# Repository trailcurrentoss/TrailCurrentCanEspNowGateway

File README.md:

# TrailCurrent CAN to ESP-NOW Gateway

A wireless relay gateway that bridges CAN bus messages to ESP-NOW protocol for remote vehicle monitoring in tow vehicles. Part of the [TrailCurrent](https://trailcurrent.com) open-source vehicle platform.

## Overview

This project enables wireless relaying of CAN bus messages using the ESP-NOW protocol. The gateway hardware and firmware allow real-time data from a trailer's CAN bus to be transmitted reliably to remote displays and monitoring devices in a vehicle.

**Use Case:** Display trailer sensor data (battery voltage, temperature, weight sensors, etc.) on an in-vehicle display while the vehicle and trailer are separated or connected.

## Hardware Overview

- **Function:** Bidirectional CAN-to-ESP-NOW gateway with wireless relay capability
- **Key Features:**
  - CAN bus interface for trailer systems
  - ESP32 with integrated WiFi for robust wireless communication
  - ESP-NOW protocol for low-latency, long-range communication
  - Power management for vehicle and trailer power systems
  - Hierarchical schematic design (5 sheets) for system modularity
  - Compact design for integration into vehicle tow systems

## Hardware Requirements

### Components

- **Microcontroller:**
  - ESP32-WROOM or ESP32-S3 with WiFi and Bluetooth

- **CAN Interface:**
  - CAN transceiver for reliable CAN bus communication
  - Protection circuits for robust automotive operation

- **Power Management:**
  - Buck converter (AP63203WU-7) for regulated power supply
  - Filtering and protection circuits

- **Connectors:**
  - CAN bus interface connectors
  - Power connectors
  - Debug/programming connectors

### KiCAD Library Dependencies

This project uses the consolidated [TrailCurrentKiCADLibraries](https://github.com/trailcurrentoss/TrailCurrentKiCADLibraries).

**Setup:**

```bash
# Clone the library
git clone git@github.com:trailcurrentoss/TrailCurrentKiCADLibraries.git

# Set environment variables (add to ~/.bashrc or ~/.zshrc)
export TRAILCURRENT_SYMBOL_DIR="/path/to/TrailCurrentKiCADLibraries/symbols"
export TRAILCURRENT_FOOTPRINT_DIR="/path/to/TrailCurrentKiCADLibraries/footprints"
export TRAILCURRENT_3DMODEL_DIR="/path/to/TrailCurrentKiCADLibraries/3d_models"
```

See [KICAD_ENVIRONMENT_SETUP.md](https://github.com/trailcurrentoss/TrailCurrentKiCADLibraries/blob/main/KICAD_ENVIRONMENT_SETUP.md) in the library repository for detailed setup instructions.

## Opening the Project

1. **Set up environment variables** (see Library Dependencies above)
2. **Open KiCAD:**
   ```bash
   kicad /path/to/EDA/trailecurrent-can-to-espnow-gateway/trailecurrent-can-to-espnow-gateway.kicad_pro
   ```
3. **Verify libraries load** - All symbol and footprint libraries should resolve without errors
4. **Navigate hierarchical sheets:**
   - Main gateway sheet with module interconnects
   - CAN interface circuit (isolation and termination)
   - ESP32 microcontroller and WiFi section
   - Power management circuits
   - Support and protection circuits
5. **View 3D models** - Open PCB and press `Alt+3` to view the 3D visualization
   - All 3D models should load from the consolidated library path
   - Models use relative `${TRAILCURRENT_3DMODEL_DIR}` references

## Firmware

See `src/` directory for PlatformIO-based firmware implementing CAN-to-ESP-NOW bridging.

**Key Features:**
- CAN message reception and parsing
- ESP-NOW wireless transmission
- Bidirectional communication capability
- Configuration management for CAN filters and routing
- Low-power sleep modes for extended battery life

**Setup:**
```bash
# Install PlatformIO (if not already installed)
pip install platformio

# Build firmware
pio run -d /path/to/project

# Upload to board
pio run -t upload -d /path/to/project

# Monitor serial output
pio device monitor -d /path/to/project
```

**WiFi Credentials:**

The gateway requires WiFi credentials for OTA updates and network communication.

- **Production**: WiFi credentials are delivered via CAN Bus (ID 0x01) from the TrailCurrent system
- **Development**: For standalone testing without the TrailCurrent system, create `src/secrets.h`:

```bash
# Copy the example template
cp src/secrets.h.example src/secrets.h

# Edit with your WiFi credentials
nano src/secrets.h
```

```cpp
// src/secrets.h (DO NOT COMMIT - it's in .gitignore)
const char* ssid = "YOUR_SSID_HERE";
const char* password = "YOUR_PASSWORD_HERE";
uint8_t broadcastAddress[] = {0xXX, 0xXX, 0xXX, 0xXX, 0xXX, 0xXX};
```

**Important:**
- Never commit `src/secrets.h` (it's in .gitignore)
- Use `src/secrets.h.example` as a template
- The gateway MAC address should match your hardware

**Future Enhancement:** WiFi credential configuration will be fully implemented via CAN Bus protocol, allowing credentials to be distributed from the TrailCurrent system without firmware modifications.

## System Architecture

The gateway architecture:

1. **CAN Interface:** Receives messages from trailer CAN bus
2. **ESP32 Processor:** Parses and routes messages based on configured rules
3. **ESP-NOW Radio:** Transmits to remote devices with low latency
4. **Remote Device:** Receives and displays trailer data

Supports multiple remote devices through ESP-NOW group addressing.

## Manufacturing

- **PCB Files:** Ready for fabrication via standard PCB services (JLCPCB, OSH Park, etc.)
- **BOM Generation:** Export BOM from KiCAD schematic (Tools → Generate BOM)
- **JLCPCB Assembly:** This project supports automated assembly using JLCPCB
  - See [BOM_ASSEMBLY_WORKFLOW.md](https://github.com/trailcurrentoss/TrailCurrentKiCADLibraries/blob/main/BOM_ASSEMBLY_WORKFLOW.md) for detailed assembly workflow
  - Component library includes LCSC, Mouser, and DigiKey part numbers for flexible sourcing

## Project Structure

- **EDA/trailecurrent-can-to-espnow-gateway/** - KiCAD schematic (5 sheets) and PCB design files
  - Gateway main sheet with module organization
  - CAN interface and protection circuits
  - ESP32 microcontroller and radio circuits
  - Power management and support circuits
- **src/** - Firmware source code for CAN message bridging and ESP-NOW communication
- **lib/** - Custom libraries and CAN protocol drivers
- **include/** - Header files for configuration and messaging

## Documentation

- **Main Schematic:** EDA/trailecurrent-can-to-espnow-gateway/trailecurrent-can-to-espnow-gateway.kicad_sch (with 5 sheet hierarchy)
- **PCB Layout:** EDA/trailecurrent-can-to-espnow-gateway/trailecurrent-can-to-espnow-gateway.kicad_pcb

## License

MIT License - See LICENSE file for details

This is open source hardware. You are free to use, modify, and distribute these designs for personal or commercial purposes.

## Contributing

Improvements and contributions are welcome! Please submit issues or pull requests to the main repository.

## Support

For questions about:
- **KiCAD setup:** See [KICAD_ENVIRONMENT_SETUP.md](https://github.com/trailcurrentoss/TrailCurrentKiCADLibraries/blob/main/KICAD_ENVIRONMENT_SETUP.md)
- **Library consolidation:** See [CONNECTOR_CONSOLIDATION_SUMMARY.md](https://github.com/trailcurrentoss/TrailCurrentKiCADLibraries/blob/main/CONNECTOR_CONSOLIDATION_SUMMARY.md)
- **Assembly workflow:** See [BOM_ASSEMBLY_WORKFLOW.md](https://github.com/trailcurrentoss/TrailCurrentKiCADLibraries/blob/main/BOM_ASSEMBLY_WORKFLOW.md)

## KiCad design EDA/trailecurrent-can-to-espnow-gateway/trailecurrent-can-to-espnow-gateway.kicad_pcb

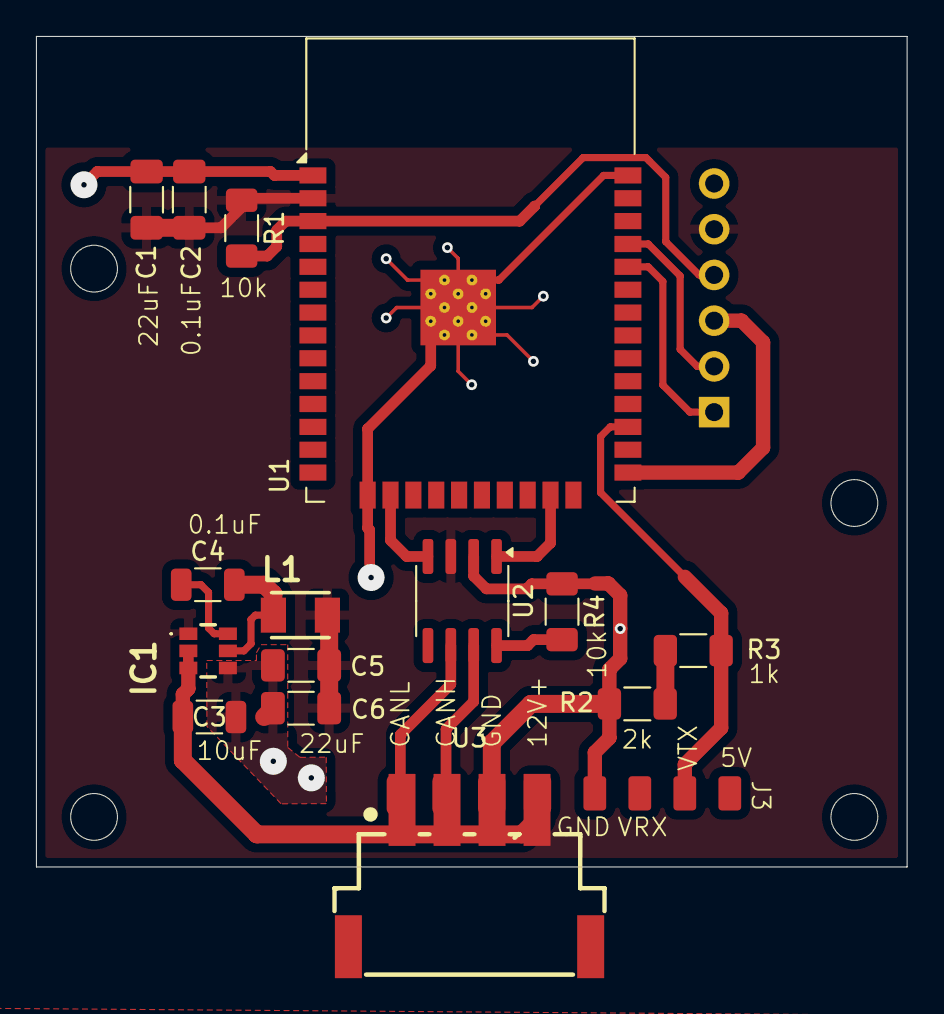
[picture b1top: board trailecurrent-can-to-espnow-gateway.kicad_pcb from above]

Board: 2 copper layers, 48.4 x 46.1 mm, 18 parts (1 on the bottom side), 16 nets.

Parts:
C1, C5, C6: 22uF; C_1206_3216Metric_Pad1.33x1.80mm_HandSolder
C2: 0.1uF; C_1206_3216Metric_Pad1.33x1.80mm_HandSolder
C3: 10uF; C_1206_3216Metric
C4: 100nF; C_1206_3216Metric
IC1: AP63203WU-7; AP63203WU7
J1: Conn_01x06; PinHeader_1x06_P2.54mm_Horizontal
J2: Conn_01x04; CAN_PLUS_POWER
J3: Conn_01x04; GenericPad_01x04
L1: NLV32T-3R9J-EF (3.9uH); NLV32T-3R9J-EF
R1, R4: 10k; R_1206_3216Metric_Pad1.30x1.75mm_HandSolder
R2: 2k; R_1206_3216Metric_Pad1.30x1.75mm_HandSolder
R3: 1k; R_1206_3216Metric_Pad1.30x1.75mm_HandSolder
U1: ESP32-WROOM-32
U2: SN65HVD230; SOIC-8_3.9x4.9mm_P1.27mm
U3: ZX-XH2.54-4PWT; CONN-SMD_4P-P2.50-WAFER-254W-4P

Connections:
+3.3V: C1.1, C2.1, C5.1, C6.1, IC1.1 (FB), J1.5, L1.2, R1.1, U1.2 (VDD), U2.3 (VCC)
+12V: C3.1, IC1.2 (EN), IC1.3 (VIN), J2.1
CANH: J2.3, U2.7 (CANH)
CANL: J2.4, U2.6 (CANL)
CAN_RX: U1.16 (IO13), U2.4 (R)
CAN_TX: U1.23 (IO15), U2.1 (D)
EN: J1.4, R1.2, U1.3 (EN)
ESP32_RX: J1.1, U1.34 (RXD0/IO3)
ESP32_TX: J1.2, U1.35 (TXD0/IO1)
GND: C1.2, C2.2, C3.2, C5.2, C6.2, IC1.4 (GND), J1.6, J2.2, J3.1, R2.1, R4.1, U1.1 (GND), U1.15 (GND), U1.38 (GND), U1.39 (GND), U2.2 (GND)
IO0: J1.3, U1.25 (IO0)
unnamed: C4.1, IC1.6 (BST)
unnamed: C4.2, IC1.5 (SW), L1.1
unnamed: R2.2, R3.1
unnamed: R4.2, U2.8 (Rs)
SHUNT_DATA: J3.3, R3.2, U1.27 (IO16)

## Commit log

2026-02-12 Initial commit: Clean migration to public Codeberg repository
    This is a fresh start on Codeberg with all security and configuration
    issues addressed:
    Security fixes:
    - Removed all git history (fresh start)
    - No personal paths or credentials exposed
    - All WiFi secrets in .gitignore (using secrets.h.example pattern)
2026-02-12 Update Codeberg URLs to trailcurrentopensource org
2026-02-14 Fixing license file
2026-02-14 Update docs: replace Codeberg URLs with GitHub references
2026-02-22 Secrets removed updated to get WiFi from OTA
2026-02-23 Add trailcurrent.com link to README
